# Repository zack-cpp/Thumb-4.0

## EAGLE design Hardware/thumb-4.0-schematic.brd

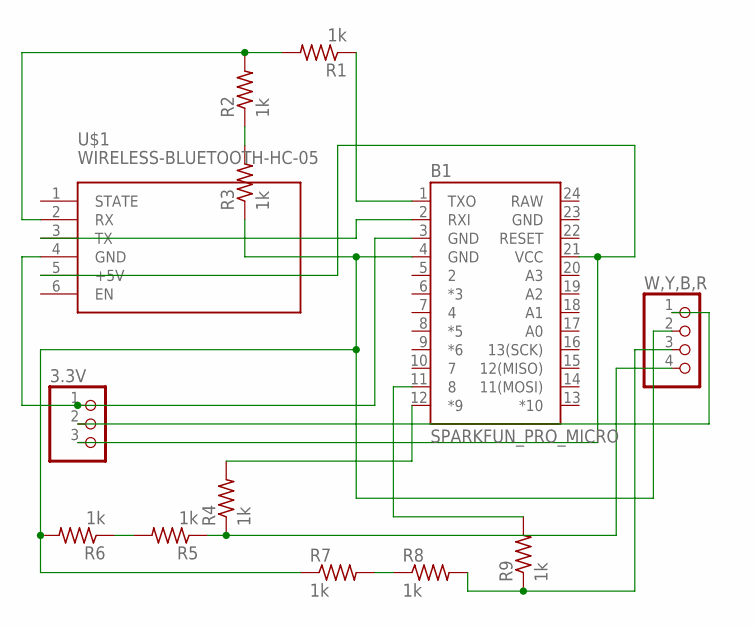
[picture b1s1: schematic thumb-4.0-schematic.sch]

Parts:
3.3V: PINHD-1X3; 1X03
B1: SPARKFUN_PRO_MICRO
R1, R2, R3, R4, R5, R6, R7, R8, R9: 1k; M1206
U$1: WIRELESS-BLUETOOTH-HC-05
W,Y,B,R: PINHD-1X4; 1X04

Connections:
GND: B1.23 (GND)
unnamed: 3.3V.1, B1.3 (GND), U$1.4 (GND)
unnamed: 3.3V.3, B1.21 (VCC), U$1.5 (+5V)
unnamed: R5.2, R6.1
unnamed: B1.12 (*9), R4.2
unnamed: B1.11 (8), R9.2
unnamed: 3.3V.2, W,Y,B,R.1
unnamed: B1.2 (RXI), U$1.3 (TX)
unnamed: R4.1, R5.1, W,Y,B,R.4
unnamed: B1.1 (TXO), R1.1
unnamed: R1.2, R2.2, U$1.2 (RX)
unnamed: R2.1, R3.2
unnamed: R8.2, R9.1, W,Y,B,R.3
unnamed: B1.4 (GND), R3.1, R6.2, R7.1, W,Y,B,R.2
unnamed: R7.2, R8.1
RAW: B1.24 (RAW)

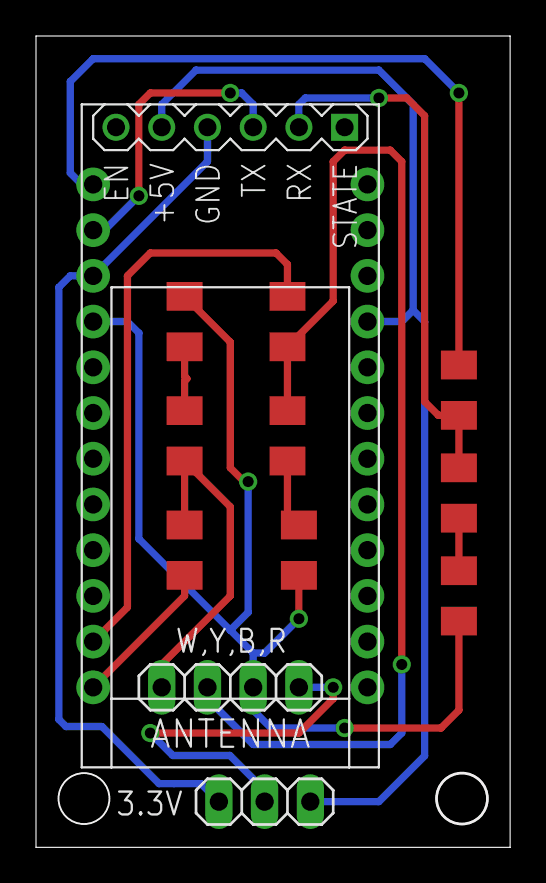
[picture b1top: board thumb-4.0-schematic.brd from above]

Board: 2 copper layers, 26.2 x 44.9 mm, 13 parts (0 on the bottom side), 14 nets.

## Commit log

2020-07-30 MCU Program
2020-07-30 Android apps for Thumb-4.0
2020-08-01 Release v1.0
2020-08-19 enclosure v1.0
2020-08-19 Schematic and Board v1.0
2020-12-05 Add "add finger" feature

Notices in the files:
parts and their libraries:
SparkFun-Boards: Licensing: Creative Commons ShareAlike 4.0 International - https://creativecommons.org/licenses/by-sa/4.0
diy-modules: Released under the Creative Commons Attribution 4.0 International License: http://creativecommons.org/licenses/by/4.0
